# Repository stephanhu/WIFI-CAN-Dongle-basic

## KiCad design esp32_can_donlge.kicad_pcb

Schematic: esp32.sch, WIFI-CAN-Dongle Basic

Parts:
D1, D2: LED; LED_0805_2012Metric
J1: Conn_01x02_Male; PinHeader_1x02_P2.54mm_Vertical
R1, R2: 1k; R_0603_1608Metric
R16, R17: 220R; R_0603_1608Metric
U1: ESP32-DevKitC-32D

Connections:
+3V3: U1.1; also elsewhere on the board
/can_interface/CAN_EN: U1.11; also elsewhere on the board
/can_interface/CAN_RX: R16.2; also elsewhere on the board
/can_interface/CAN_TERM_EN: U1.5; also elsewhere on the board
/can_interface/CAN_TX: R17.2; also elsewhere on the board
/esp32/RXD: J1.1, U1.24
/esp32/TEST_LED0: R1.1, U1.28
/esp32/TEST_LED1: R2.1, U1.27
/esp32/TXD: J1.2, U1.23
BAT_ADC_IN: U1.6; also elsewhere on the board
GND: D1.1, D2.1, U1.14, U1.20, U1.26; also elsewhere on the board
unnamed: D1.2, R1.2
unnamed: D2.2, R2.2
unnamed: R16.1, U1.25
unnamed: R17.1, U1.22

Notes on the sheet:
Global Label
Hierachical Label
Local Label
Remove diode D3 from ESP32-DevKitC https://dl.espressif.com/dl/schematics/esp32_devkitc_v4-sch-20180607a.pdf

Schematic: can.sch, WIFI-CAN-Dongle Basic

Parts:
C8: 100n/25V; C_0603_1608Metric
C9: 10u/25V; C_0805_2012Metric
R18: 0R; R_0603_1608Metric
R19, R20: 10k; R_0603_1608Metric
R21: 1k; R_0603_1608Metric
R22: 470R; R_0603_1608Metric
R23: 100R; R_0603_1608Metric
U2: SN65HVD230DR; SOIC-8_3.9x4.9mm_P1.27mm; MPN SN65HVD230DR
U3: TLP175A; MFSOP6-4_4.4x3.6mm_P1.27mm; MPN TLP175A

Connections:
+3V3: C8.1, C9.1, R19.1, R21.1, U2.3; also elsewhere on the board
/can_interface/CAN_EN: R18.2; also elsewhere on the board
/can_interface/CAN_N: U2.6, U3.4; also elsewhere on the board
/can_interface/CAN_P: R23.1, U2.7; also elsewhere on the board
/can_interface/CAN_RX: U2.4; also elsewhere on the board
/can_interface/CAN_TERM_EN: R22.2; also elsewhere on the board
/can_interface/CAN_TX: U2.1; also elsewhere on the board
GND: C8.2, C9.2, R20.2, U2.2, U3.3; also elsewhere on the board
unnamed: R18.1, R21.2, U2.8
unnamed: R19.2, R20.1, U2.5
unnamed: R22.1, U3.1
unnamed: R23.2, U3.6

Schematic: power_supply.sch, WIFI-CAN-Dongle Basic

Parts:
D4: NUP2105L; SOT-23; MPN NUP2105L
D5: B130-E3; D_SMA
J3: DB9_Male; DSUB-9_Male_EdgeMount_P2.77mm
R26: 82k; R_0603_1608Metric
R27: 33k; R_0603_1608Metric
U4: OKI-78SR; TO-220-3_Horizontal_TabDown

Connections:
+3V3: U4.3; also elsewhere on the board
+12V: D5.1 (K), U4.1
/can_interface/CAN_N: D4.1, J3.2; also elsewhere on the board
/can_interface/CAN_P: D4.2, J3.7; also elsewhere on the board
/power_supply/V_BAT: D5.2 (A), J3.9, R26.1
BAT_ADC_IN: R26.2, R27.1; also elsewhere on the board
GND: D4.3, J3.3, R27.2, U4.2; also elsewhere on the board

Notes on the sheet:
add heat shrink tube to OKI

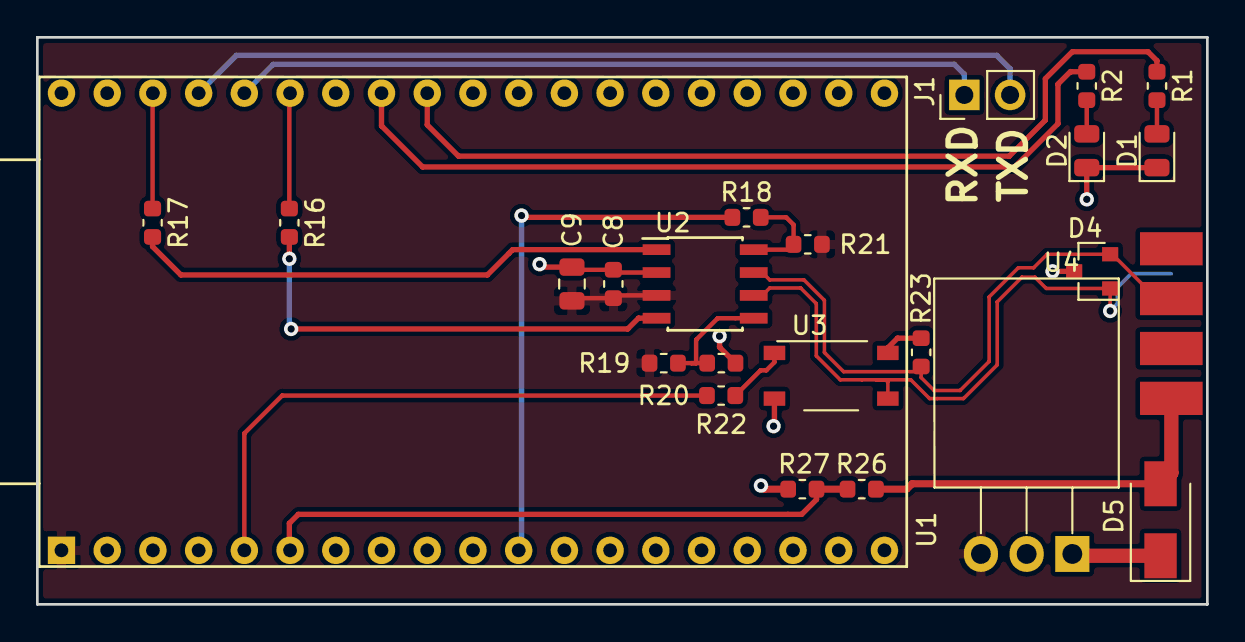
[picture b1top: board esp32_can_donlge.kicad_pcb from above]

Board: 2 copper layers, 65.0 x 31.5 mm, 24 parts (1 on the bottom side), 23 nets.

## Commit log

2018-10-03 changed to a more basic variant of the esp32
2018-10-04 minor changes in schematic, fixed wrong footprint of voltage regulator
